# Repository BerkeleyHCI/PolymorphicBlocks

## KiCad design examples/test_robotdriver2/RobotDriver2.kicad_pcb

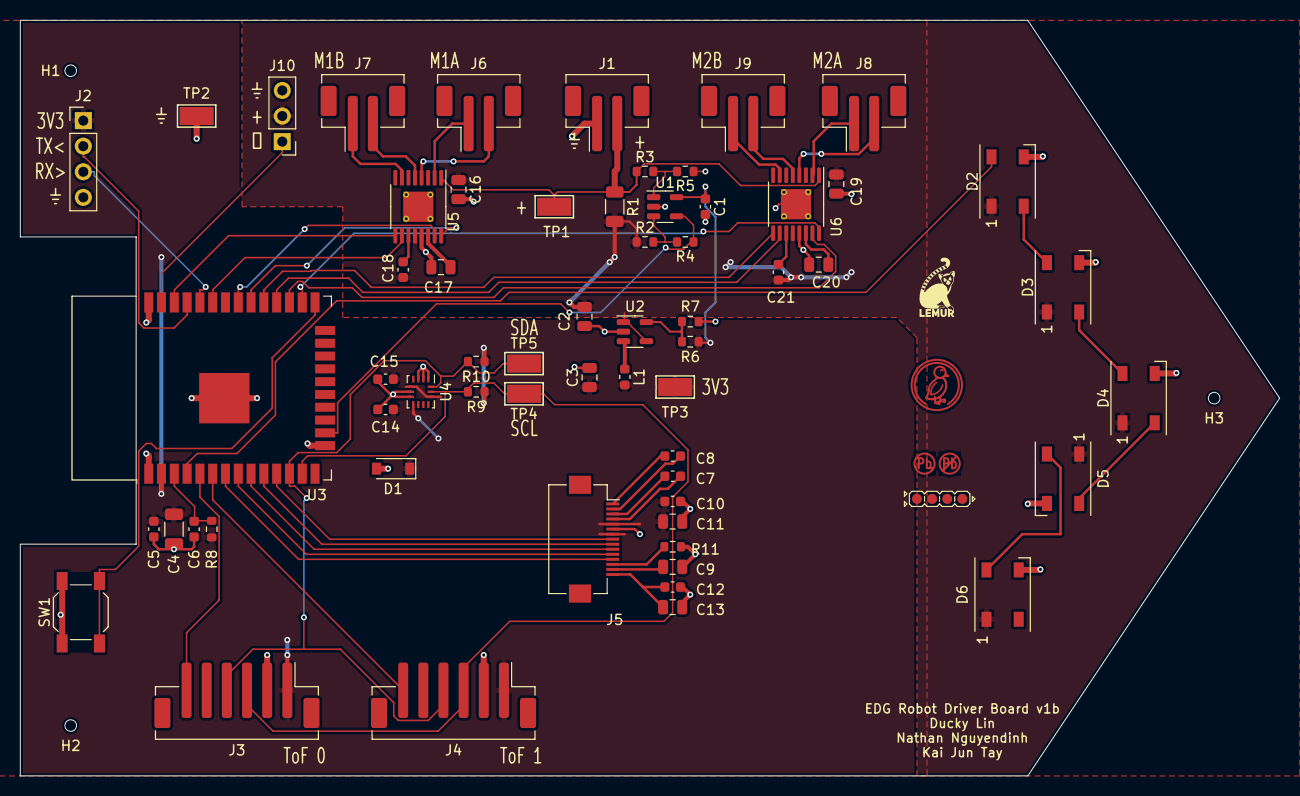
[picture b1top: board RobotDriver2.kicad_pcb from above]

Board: 2 copper layers, 125.0 x 75.0 mm, 68 parts (0 on the bottom side), 55 nets.

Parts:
C1, C5, C7, C8, C10, C12, C14, C15: C14663; C_0603_1608Metric
C2, C3, C9, C11, C17, C20: C1779; C_0805_2012Metric
C4: C5672; C_1206_3216Metric
C6: C15849; C_0603_1608Metric
C13, C16, C19: C15850; C_0805_2012Metric
C18, C21: C57112; C_0603_1608Metric
D1: C499796; D_SOD-123
D2, D3, D4, D5, D6: C2920042; LED_WS2812B_PLCC4_5.0x5.0mm_P3.2mm
H1, H2, H3: JlcToolingHole_1.152mm
J1, J6, J7, J8, J9: C64658; JST_PH_B2B-PH-SM4-TB_1x02-1MP_P2.00mm_Vertical
J2: PinHeader_1x04_P2.54mm_Vertical
J3, J4: C265088; JST_PH_B6B-PH-SM4-TB_1x06-1MP_P2.00mm_Vertical
J5: Hirose_FH12-15S-0.5SH_1x15-1MP_P0.50mm_Horizontal
J10: PinHeader_1x03_P2.54mm_Vertical
L1: C295681; L_0603_1608Metric
R1: C411236; R_1206_3216Metric
R2, R3, R8: C25804; R_0603_1608Metric
R4, R5: C25803; R_0603_1608Metric
R6: C23231; R_0603_1608Metric
R7: C22809; R_0603_1608Metric
R9, R10: C23162; R_0603_1608Metric
R11: C23203; R_0603_1608Metric
SW1: C318884; SW_SPST_SKQG_WithoutStem
TP1, TP2, TP3, TP4, TP5: C238130; TestPoint_Keystone_5015_Micro-Minature
U1: C7972; SOT-23-5
U2: C500769; SOT-23-5
U3: C701342; ESP32-WROOM-32
U4: C967633; Bosch_LGA-14_3x2.5mm_P0.5mm
U5, U6: C50506; TSSOP-16-1EP_4.4x5mm_P0.65mm_EP3x3mm_ThermalVias
U7: Symbol_LemurSmall
U8: Symbol_Duckling
U9: Indicator_LeadFree
U10: Indicator_IdDots_4

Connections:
batt.pins.2: J1.2, R1.1, R3.1, TP1.1, U5.1, U6.1
gnd: C1.2, C2.2, C3.2, C4.2, C5.2, C6.2, C9.2, C10.2, C11.2, C12.2, C13.2, C14.2, C15.2, C16.2, C17.2, C19.2, C20.2, D1.2, D2.3, D3.3, D4.3, D5.3, D6.3, J1.1, J2.4, J3.2, J4.2, J5.6, J10.3, R5.1, R7.2, R11.2, SW1.1, TP2.1, U1.2, U2.2, U3.1, U3.15, U3.38, U3.39, U4.1, U4.2, U4.3, U4.6, U4.7, U5.13, U5.17, U6.13, U6.17
i2c_chain_0.scl: J3.3, J4.3, R9.2, TP4.1, U3.13, U4.13
i2c_chain_0.sda: J3.4, J4.4, R10.2, TP5.1, U3.12, U4.14
isense.amp.(adapter)rf.b.dst: R2.2, R4.2, U1.3
isense.amp.rg.b: R3.2, R5.2, U1.1
lcd.c2_cap.neg: C8.2, J5.2
lcd.device.c1n: C7.2, J5.4
lcd.device.c1p: C7.1, J5.3
lcd.device.c2p: C8.1, J5.1
lcd.device.iref: J5.13, R11.1
lcd.device.vcomh: C9.1, J5.14
lcd.spi.mosi: J5.12, U3.7
lcd.spi.sck: J5.11, U3.8
lcd.vcc_cap2.pos: C12.1, C13.1, J5.15
m1_a.pins.1: J6.1, U5.2
m1_a.pins.2: J6.2, U5.4
m1_b.pins.1: J7.1, U5.7
m1_b.pins.2: J7.2, U5.5
m2_a.pins.1: J8.1, U6.2
m2_a.pins.2: J8.2, U6.4
m2_b.pins.1: J9.1, U6.7
m2_b.pins.2: J9.2, U6.5
mcu.adc.isense: R4.1, U1.4, U3.16
mcu.en_pull.output: C6.1, R8.2, U3.3
mcu.gpio.lcd_cs: J5.8, U3.11
mcu.gpio.lcd_dc: J5.10, U3.9
mcu.gpio.lcd_reset: J5.9, U3.10
mcu.gpio.ledArray: D2.4, U3.4
mcu.gpio.motor_1a1: U3.30, U5.16
mcu.gpio.motor_1a2: U3.31, U5.15
mcu.gpio.motor_1b1: U3.36, U5.9
mcu.gpio.motor_1b2: U3.33, U5.10
mcu.gpio.motor_2a1: U3.26, U6.16
mcu.gpio.motor_2a2: U3.27, U6.15
mcu.gpio.motor_2b1: U3.29, U6.9
mcu.gpio.motor_2b2: U3.28, U6.10
mcu.gpio.pwm: J10.1, U3.37
mcu.gpio.tof_xshut_0: J3.6, U3.5
mcu.gpio.tof_xshut_1: J4.6, U3.6
mcu.prog.out: SW1.2, U3.25
mcu.uart0.uart.rx: J2.2, U3.35
mcu.uart0.uart.tx: J2.3, U3.34
motor_driver1.ic.vcp: C18.1, U5.11
motor_driver1.vint_cap.pwr: C17.1, U5.14
motor_driver2.ic.vcp: C21.1, U6.11
motor_driver2.vint_cap.pwr: C20.1, U6.14
reg_3v3.fb.center: R6.2, R7.1, U2.5
reg_3v3.power_path.switch: L1.1, U2.3
v3v3: C1.1, C3.1, C4.1, C5.1, C10.1, C11.1, C14.1, C15.1, D1.1, J2.1, J3.1, J4.1, J5.5, J5.7, L1.2, R6.1, R8.1, R9.1, R10.1, TP3.1, U1.5, U3.2, U4.5, U4.8, U4.12
vbatt: C2.1, C16.1, C18.2, C19.1, C21.2, D2.1, D3.1, D4.1, D5.1, D6.1, J10.2, R1.2, R2.1, U2.1, U2.4, U5.12, U6.12
ws2812bArray.led[1].din: D2.2, D3.4
ws2812bArray.led[1].dout: D3.2, D4.4
ws2812bArray.led[3].din: D4.2, D5.4
ws2812bArray.led[4].din: D5.2, D6.4

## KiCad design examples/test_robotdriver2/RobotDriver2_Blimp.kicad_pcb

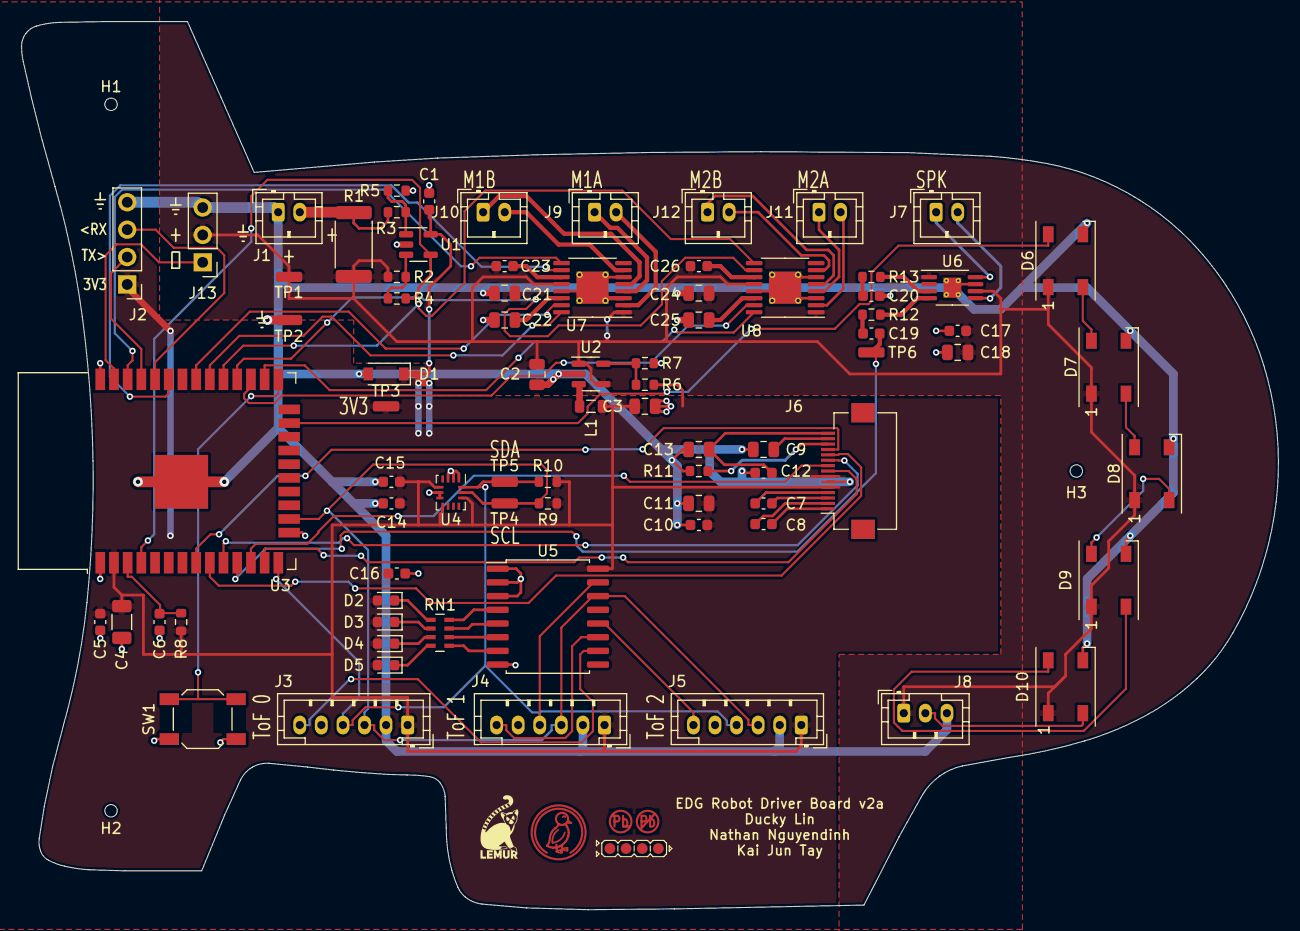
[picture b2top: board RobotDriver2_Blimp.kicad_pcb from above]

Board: 2 copper layers, 116.5 x 82.3 mm, 86 parts (0 on the bottom side), 72 nets.

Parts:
C1, C5, C7, C8, C10, C12, C14, C15, C16, C17: C14663; C_0603_1608Metric
C2, C3, C9, C11, C18, C22, C25: C1779; C_0805_2012Metric
C4: C5672; C_1206_3216Metric
C6, C19, C20: C15849; C_0603_1608Metric
C13, C21, C24: C15850; C_0805_2012Metric
C23, C26: C57112; C_0603_1608Metric
D1: C499796; D_SOD-123
D2, D3, D4, D5: C2286; LED_0603_1608Metric
D6, D7, D8, D9, D10: C2920042; LED_WS2812B_PLCC4_5.0x5.0mm_P3.2mm
H1, H2, H3: JlcToolingHole_1.152mm
J1, J7, J9, J10, J11, J12: JST_PH_B2B-PH-K_1x02_P2.00mm_Vertical
J2: PinHeader_1x04_P2.54mm_Vertical
J3, J4, J5: JST_PH_B6B-PH-K_1x06_P2.00mm_Vertical
J6: Hirose_FH12-15S-0.5SH_1x15-1MP_P0.50mm_Horizontal
J8: JST_PH_B3B-PH-K_1x03_P2.00mm_Vertical
J13: PinHeader_1x03_P2.54mm_Vertical
L1: C98331; L_0805_2012Metric
R1: C305115; R_2512_6332Metric
R2, R3, R8: C25804; R_0603_1608Metric
R4, R5: C25811; R_0603_1608Metric
R6: C23231; R_0603_1608Metric
R7: C22809; R_0603_1608Metric
R9, R10: C23162; R_0603_1608Metric
R11: C23203; R_0603_1608Metric
R12, R13: C22984; R_0603_1608Metric
RN1: C20197; R_Array_Concave_4x0603
SW1: C318884; SW_SPST_SKQG_WithoutStem
TP1, TP2, TP3, TP4, TP5, TP6: TestPoint_TE_RCU_0603
U1: C7972; SOT-23-5
U2: C500769; SOT-23-5
U3: C701342; ESP32-WROOM-32
U4: C967633; Bosch_LGA-14_3x2.5mm_P0.5mm
U5: C86832; SOIC-16W_7.5x10.3mm_P1.27mm
U6: C27396; MSOP-8-1EP_3x3mm_P0.65mm_EP1.68x1.88mm_ThermalVias
U7, U8: C50506; TSSOP-16-1EP_4.4x5mm_P0.65mm_EP3x3mm_ThermalVias
U9: Symbol_LemurSmall
U10: Symbol_Duckling
U11: Indicator_LeadFree
U12: Indicator_IdDots_4

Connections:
batt.pins.2: J1.2, R1.1, R3.1
expander.io.led_1: RN1.7, U5.5
expander.io.led_2: RN1.6, U5.6
expander.io.tof_xshut_0: J3.6, U5.10
expander.io.tof_xshut_1: J4.6, U5.11
gnd: C1.2, C2.2, C3.2, C4.2, C5.2, C6.2, C9.2, C10.2, C11.2, C12.2, C13.2, C14.2, C15.2, C16.2, C17.2, C18.2, C20.2, C21.2, C22.2, C24.2, C25.2, D1.2, D6.3, D7.3, D8.3, D9.3, D10.3, J1.1, J2.4, J3.2, J4.2, J5.2, J6.6, J8.3, J13.3, R5.1, R7.2, R11.2, SW1.1, TP2.1, U1.2, U2.2, U3.1, U3.15, U3.38, U3.39, U4.1, U4.2, U4.3, U4.6, U4.7, U5.1, U5.2, U5.3, U5.8, U6.7, U6.9, U7.3, U7.6, U7.13, U7.17, U8.3, U8.6, U8.13, U8.17
i2c_chain_0.scl: J3.3, J4.3, J5.3, R9.2, TP4.1, U3.16, U4.13, U5.14
i2c_chain_0.sda: J3.4, J4.4, J5.4, R10.2, TP5.1, U3.14, U4.14, U5.15
isense.amp.(adapter)r2.b.src: R3.2, R5.2, U1.1
isense.amp.(adapter)rf.b.src: R2.2, R4.2, U1.3
lcd.c1_cap.pos: C7.1, J6.3
lcd.c2_cap.pos: C8.1, J6.1
lcd.device.c1n: C7.2, J6.4
lcd.device.c2n: C8.2, J6.2
lcd.device.iref: J6.13, R11.1
lcd.spi.mosi: J6.12, U3.8
lcd.spi.sck: J6.11, U3.9
lcd.vcc_cap2.pwr: C12.1, C13.1, J6.15
lcd.vcomh_cap.pos: C9.1, J6.14
led_pixel.pins.2: D10.2, J8.2
led_res.a.0: D2.1, RN1.1
led_res.a.1: D3.1, RN1.2
led_res.a.2: D4.1, RN1.3
led_res.a.3: D5.1, RN1.4
led_res.b.0: RN1.8, U5.4
leds.signals.3: RN1.5, U5.7
m1_a.pins.1: J9.1, U7.4
m1_a.pins.2: J9.2, U7.2
m1_b.pins.1: J10.1, U7.5
m1_b.pins.2: J10.2, U7.7
m2_a.pins.1: J11.1, U8.4
m2_a.pins.2: J11.2, U8.2
m2_b.pins.1: J12.1, U8.5
m2_b.pins.2: J12.2, U8.7
mcu.adc.isense: R4.1, U1.4, U3.4
mcu.gpio.lcd_cs: J6.8, U3.13
mcu.gpio.lcd_dc: J6.10, U3.10
mcu.gpio.lcd_reset: J6.9, U3.12
mcu.gpio.ledArray: D6.4, U3.23
mcu.gpio.motor_1a1: U3.30, U7.16
mcu.gpio.motor_1a2: U3.31, U7.15
mcu.gpio.motor_1b1: U3.36, U7.9
mcu.gpio.motor_1b2: U3.33, U7.10
mcu.gpio.motor_2a1: U3.26, U8.16
mcu.gpio.motor_2a2: U3.27, U8.15
mcu.gpio.motor_2b1: U3.29, U8.9
mcu.gpio.motor_2b2: U3.28, U8.10
mcu.ic.chip_pu: C6.1, R8.2, U3.3
mcu.ic.io0: SW1.2, U3.25
mcu.ic.uart0.tx: J2.2, U3.35
mcu.uart0.uart.tx: J2.3, U3.34
motor_driver1.ic.vcp: C23.1, U7.11
motor_driver1.vint_cap.pwr: C22.1, U7.14
motor_driver2.ic.vcp: C26.1, U8.11
motor_driver2.vint_cap.pwr: C25.1, U8.14
reg_3v3.fb.output: R6.2, R7.1, U2.5
reg_3v3.ic.sw: L1.1, U2.3
servo.pins.1: J13.1, U3.37
spk_chain_0: C19.2, TP6.1, U3.11
spk_chain_1.a: J7.1, U6.8
spk_chain_1.b: J7.2, U6.5
spk_drv.(adapter)inn_res.b.src: R13.2, U6.3
spk_drv.(adapter)inp_res.b.src: R12.2, U6.4
spk_drv.inn_cap.pos: C20.1, R13.1
spk_drv.inp_res.a: C19.1, R12.1
tof.xshut.2: J5.6, U5.12
v3v3: C1.1, C3.1, C4.1, C5.1, C10.1, C11.1, C14.1, C15.1, C16.1, D1.1, D2.2, D3.2, D4.2, D5.2, J2.1, J3.1, J4.1, J5.1, J6.5, J6.7, L1.2, R6.1, R8.1, R9.1, R10.1, TP3.1, U1.5, U3.2, U4.5, U4.8, U4.12, U5.16
vbatt: C2.1, C17.1, C18.1, C21.1, C23.2, C24.1, C26.2, D6.1, D7.1, D8.1, D9.1, D10.1, J8.1, J13.2, R1.2, R2.1, TP1.1, U2.1, U2.4, U6.1, U6.6, U7.1, U7.12, U8.1, U8.12
ws2812bArray.led[1].din: D6.2, D7.4
ws2812bArray.led[1].dout: D7.2, D8.4
ws2812bArray.led[3].din: D8.2, D9.4
ws2812bArray.led[3].dout: D9.2, D10.4

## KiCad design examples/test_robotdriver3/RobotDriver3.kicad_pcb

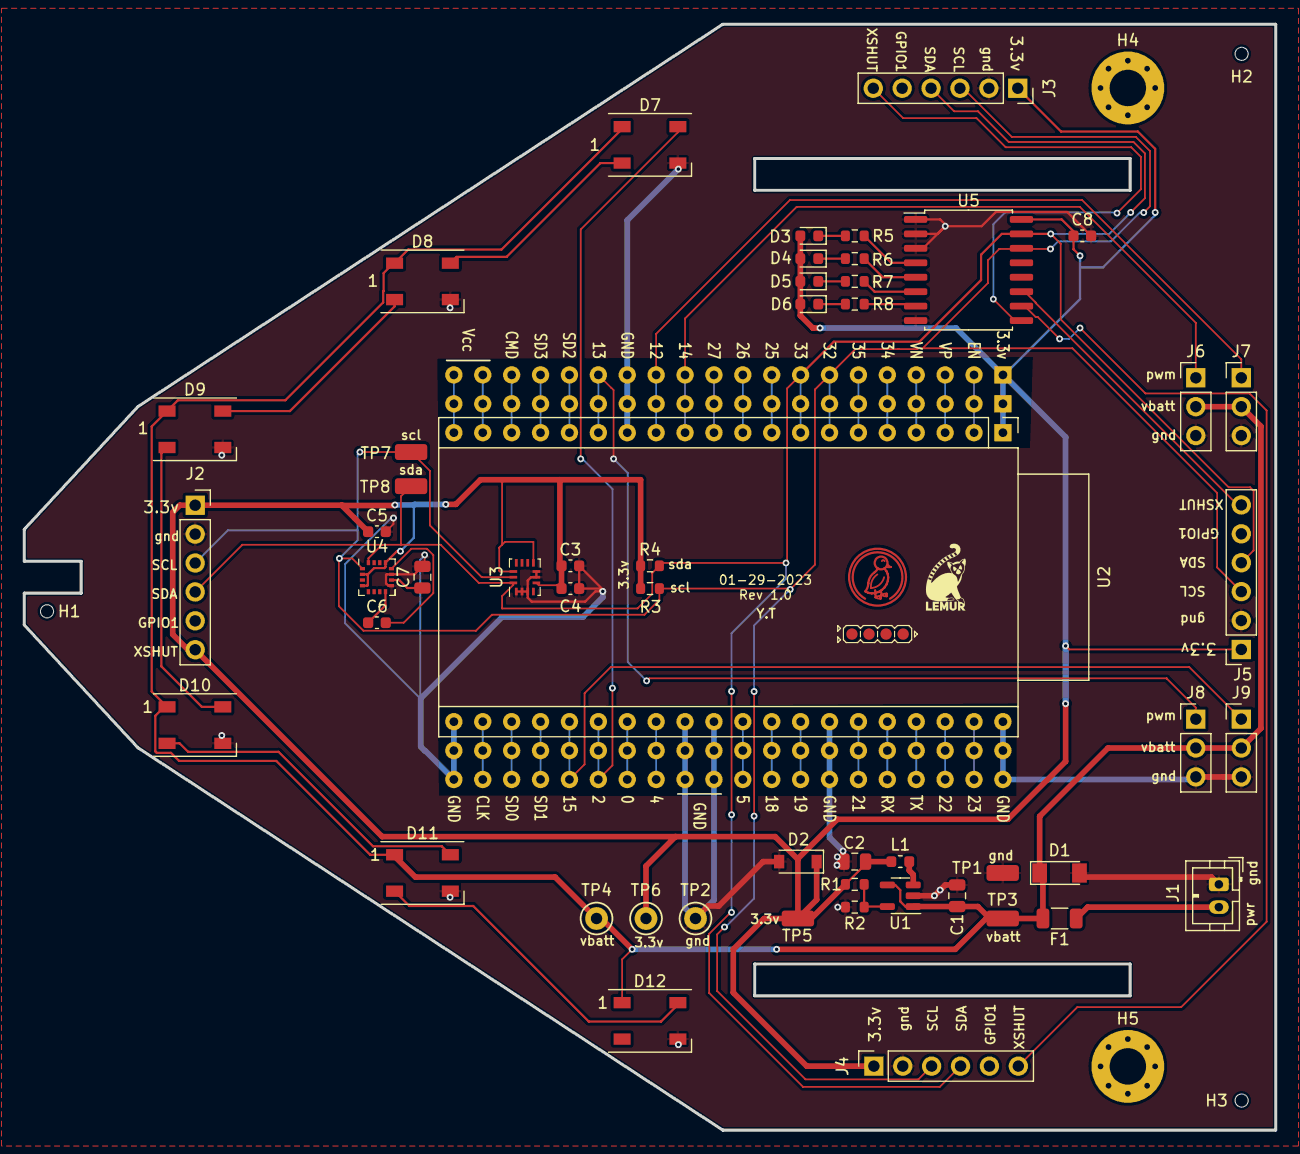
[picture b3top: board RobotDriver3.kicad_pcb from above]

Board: 2 copper layers, 110.0 x 97.2 mm, 60 parts (0 on the bottom side), 32 nets.

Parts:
C1, C2, C7: C_0805_2012Metric
C3, C4, C5, C6, C8: C_0603_1608Metric
D1: ZMM5V6-M (ST(Semtech)) - 100nA@1V 25? Single 5.2V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; D_MiniMELF
D2: BZT52C3V6 (SMC(Sangdest Microelectronicstronic (N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; D_SOD-123
D3, D4, D5, D6: KT-0603R (Hubei KENTO Elec) - Red 615~630nm 1.9~2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; LED_0603_1608Metric
D7, D8, D9, D10, D11, D12: WS2812B (Worldsemi); LED_WS2812B_PLCC4_5.0x5.0mm_P3.2mm
F1: MF-NSMF200-2 (BOURNS) - 6V 2A 100A 4A 1206 Resett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; R_1206_3216Metric
H1, H2, H3: JlcToolingHole_1.152mm
H4, H5: M3; MountingHole_3.2mm_M3_Pad_Via
J1: B2B-PH-K (JST); JST_PH_B2B-PH-K_1x02_P2.00mm_Vertical
J2, J3, J4, J5: PinSocket2.54 1x6 (Generic); PinSocket_1x06_P2.54mm_Vertical
J6, J7, J8, J9: PinHeader2.54 1x3 (Generic); PinHeader_1x03_P2.54mm_Vertical
L1: L_0603_1608Metric
R1, R2, R3, R4, R5, R6, R7, R8: R_0603_1608Metric
TP1: 5015 (Keystone) - gnd; TestPoint_TE_RCT_0805
TP2: 5001 (Keystone) - gnd; TestPoint_Keystone_5000-5004_Miniature
TP3: 5015 (Keystone) - vbatt; TestPoint_TE_RCT_0805
TP4: 5001 (Keystone) - vbatt; TestPoint_Keystone_5000-5004_Miniature
TP5: 5015 (Keystone) - v3v3; TestPoint_TE_RCT_0805
TP6: 5001 (Keystone) - v3v3; TestPoint_Keystone_5000-5004_Miniature
TP7: 5015 (Keystone) - i2c_chain_0.scl; TestPoint_TE_RCT_0805
TP8: 5015 (Keystone) - i2c_tp._io_sda_link; TestPoint_TE_RCT_0805
U1: AP3418 (Diodes Incorporated); SOT-23-5
U2: ESP32-WROVER-DEV; ESP32-WROVER-DEV_Chicken
U3: LSM6DS3TR-C (STMicroelectronics); Bosch_LGA-14_3x2.5mm_P0.5mm
U4: QMC5883L (QST); LGA-16_3x3mm_P0.5mm
U5: PCF8574AT (NXP); SOIC-16W_7.5x10.3mm_P1.27mm
U6: Lemur; Symbol_LemurSmall
U7: Duck; Symbol_Duckling
U8: IdDots4; Indicator_IdDots_4

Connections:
batt.pwr: F1.1, J1.2
expander.io.led_0: R5.2, U5.4
expander.io.led_1: R6.2, U5.5
expander.io.led_2: R7.2, U5.6
expander.io.led_3: R8.2, U5.7
expander.io.tof_xshut_1: J3.6, U5.9
expander.io.tof_xshut_2: J4.6, U5.10
expander.io.tof_xshut_3: J5.6, U5.11
gnd: C1.2, C2.2, C3.2, C4.2, C5.2, C7.2, C8.2, D1.2, D2.2, D7.3, D8.3, D9.3, D10.3, D11.3, D12.3, J1.1, J2.2, J3.2, J4.2, J5.2, J6.3, J7.3, J8.3, J9.3, R2.2, TP1.1, TP2.1, U1.2, U2.14, U2.21, U2.29, U2.30, U2.34, U2.40, U3.1, U3.2, U3.3, U3.6, U3.7, U4.9, U4.11, U5.1, U5.2, U5.3, U5.8
i2c_chain_0.scl: J2.3, J3.3, J4.3, J5.3, R3.2, TP7.1, U2.7, U3.13, U4.1, U5.14
i2c_chain_0.sda: J2.4, J3.4, J4.4, J5.4, R4.2, TP8.1, U2.8, U3.14, U4.16, U5.15
leds.led[0].res.a: D3.1, R5.1
leds.led[1].res.a: D4.1, R6.1
leds.led[2].res.a: D5.1, R7.1
leds.led[3].res.a: D6.1, R8.1
mag.c1.pos: C7.1, U4.10
mag.set_cap.neg: C6.2, U4.12
mag.set_cap.pos: C6.1, U4.8
mcu.io2: D7.4, U2.26
reg_3v3.fb.output: R1.2, R2.1, U1.5
reg_3v3.power_path.switch: L1.1, U1.3
servo[0].pwm: J6.1, U2.12
servo[1].pwm: J7.1, U2.13
servo[2].pwm: J8.1, U2.15
servo[3].pwm: J9.1, U2.25
v3v3: C2.1, C3.1, C4.1, C5.1, C8.1, D2.1, D3.2, D4.2, D5.2, D6.2, J2.1, J2.6, J3.1, J4.1, J5.1, L1.2, R1.1, R3.1, R4.1, TP5.1, TP6.1, U2.1, U3.5, U3.8, U3.12, U4.2, U4.4, U4.13, U5.16
vbatt: C1.1, D1.1, D7.1, D8.1, D9.1, D10.1, D11.1, D12.1, F1.2, J6.2, J7.2, J8.2, J9.2, TP3.1, TP4.1, U1.1, U1.4
ws2812bArray.led[0].dout: D7.2, D8.4
ws2812bArray.led[1].dout: D8.2, D9.4
ws2812bArray.led[2].dout: D9.2, D10.4
ws2812bArray.led[3].dout: D10.2, D11.4
ws2812bArray.led[4].dout: D11.2, D12.4

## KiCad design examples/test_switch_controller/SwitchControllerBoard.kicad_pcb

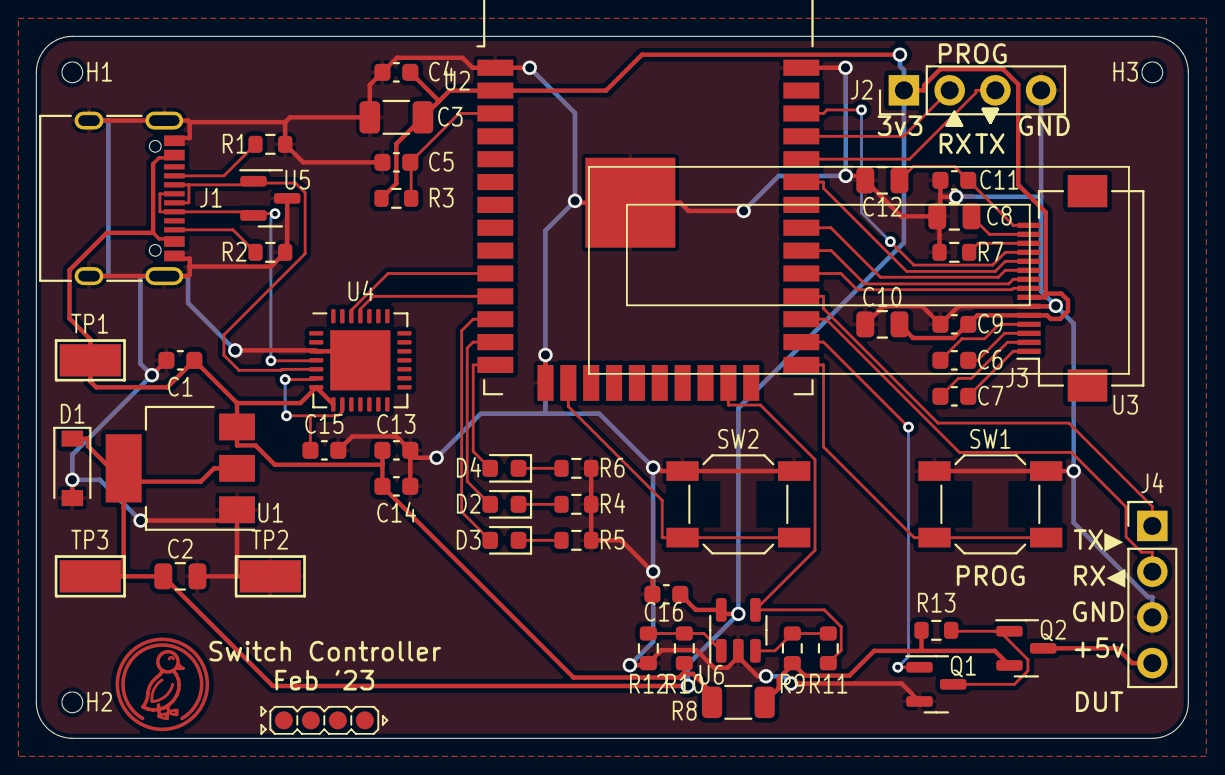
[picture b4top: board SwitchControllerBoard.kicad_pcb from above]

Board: 2 copper layers, 64.0 x 39.0 mm, 55 parts (0 on the bottom side), 42 nets.

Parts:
C1, C4, C5, C6, C7, C9, C11, C13, C14, C15, C16: C_0603_1608Metric
C2, C8, C10, C12: C_0805_2012Metric
C3: C_1206_3216Metric
D1: BZT52C3V6 (SMC(Sangdest Microelectronicstronic (N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; D_SOD-123
D2: KT-0603R (Hubei KENTO Elec) - Red 615~630nm 1.9~2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; LED_0603_1608Metric
D3, D4: LED_0603_1608Metric
H1, H2, H3: JlcToolingHole_1.152mm
J1: COM-15111 (Sparkfun); USB_C_Receptacle_XKB_U262-16XN-4BVC11
J2, J4: PinHeader2.54 1x4 (Generic); PinHeader_1x04_P2.54mm_Vertical
J3: AFC01-S15FCA-00 (Jushuo); Hirose_FH12-15S-0.5SH_1x15-1MP_P0.50mm_Horizontal
Q1: 2N7002 (Changjiang Electronics Tech (CJ)) - 60V 1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; SOT-23
Q2: AO3401A (Alpha & Omega Semicon) - 30V 4A 44m?@10V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; SOT-23
R1, R2, R3, R4, R5, R6, R7, R9, R10, R11, R12, R13: R_0603_1608Metric
R8: R_1206_3216Metric
SW1, SW2: 5.1mm switch; SW_SPST_SKQG_WithoutStem
TP1: 5015 (Keystone) - vusb; TestPoint_Keystone_5015_Micro-Minature
TP2: 5015 (Keystone) - gnd; TestPoint_Keystone_5015_Micro-Minature
TP3: 5015 (Keystone) - v3v3; TestPoint_Keystone_5015_Micro-Minature
U1: LD1117S33TR (STMicroelectronics); SOT-223-3_TabPin2
U2: ESP32-WROOM-32 (Espressif Systems); ESP32-WROOM-32
U3: ER-OLED-0.91-e (EastRising); Lcd_Er_Oled0.91_3_Outline
U4: CP2102 (Silicon Labs); QFN-28-1EP_5x5mm_P0.5mm_EP3.35x3.35mm
U5: PESD5V0X1BT (Nexperia); SOT-23
U6: LMV321 (Texas Instruments); SOT-23-5
U7: Duck; Symbol_Duckling
U8: IdDots4; Indicator_IdDots_4

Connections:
conn.uart.rx: J4.1, U2.28
conn.uart.tx: J4.2, U2.27
gnd: C1.2, C2.2, C3.2, C4.2, C5.2, C8.2, C9.2, C10.2, C11.2, C12.2, C13.2, C14.2, C15.2, C16.2, D1.2, J1.A1, J1.A12, J1.B1, J1.B12, J1.S1, J2.4, J3.6, J4.3, Q1.2, R1.1, R2.1, R4.2, R5.2, R6.2, R7.2, R12.1, SW1.1, SW2.1, TP2.1, U1.1, U2.1, U2.15, U2.38, U2.39, U4.3, U4.29, U5.3, U6.2
isense.amp.r1.b: R9.2, R11.2, U6.3
isense.amp.r2.b: R10.2, R12.2, U6.1
isense.out: R11.1, U2.23, U6.4
isense.pwr_out: Q2.2, R8.2, R9.1, R13.1
lcd.c1_cap.neg: C6.2, J3.4
lcd.c1_cap.pos: C6.1, J3.3
lcd.c2_cap.neg: C7.2, J3.2
lcd.c2_cap.pos: C7.1, J3.1
lcd.cs: J3.8, U2.29
lcd.dc: J3.10, U2.31
lcd.device.vcc: C11.1, C12.1, J3.15
lcd.device.vcomh: C8.1, J3.14
lcd.iref_res.a: J3.13, R7.1
lcd.reset: J3.9, U2.30
lcd.spi.mosi: J3.12, U2.36
lcd.spi.sck: J3.11, U2.33
ledb.res.a: D4.1, R6.1
ledb.signal: D4.2, U2.14
ledg.res.a: D3.1, R5.1
ledg.signal: D3.2, U2.12
ledr.res.a: D2.1, R4.1
ledr.signal: D2.2, U2.13
mcu.ic.chip_pu: C5.1, R3.2, U2.3
mcu.prog.out: SW1.2, U2.25
mcu.uart0.uart.rx: J2.2, U2.35
mcu.uart0.uart.tx: J2.3, U2.34
sw1.out: SW2.2, U2.16
sw.control: Q1.1, U2.26
sw.output: J4.4, Q2.3
sw.pre.drain: Q1.3, Q2.1, R13.2
usb.conn.A5: J1.A5, R1.2
usb.conn.B5: J1.B5, R2.2
usb.usb.dm: J1.A7, J1.B7, U4.5, U5.1
usb.usb.dp: J1.A6, J1.B6, U4.4, U5.2
usb_uart.ic.vdd: C15.1, U4.6, U4.9
usb_uart.uart.rx: U2.11, U4.25
usb_uart.uart.tx: U2.10, U4.26
v3v3: C2.1, C3.1, C4.1, C9.1, C10.1, C16.1, D1.1, J2.1, J3.5, J3.7, R3.1, TP3.1, U1.2, U2.2, U6.5
vusb: C1.1, C13.1, C14.1, J1.A4, J1.A9, J1.B4, J1.B9, R8.1, R10.1, TP1.1, U1.3, U4.7, U4.8

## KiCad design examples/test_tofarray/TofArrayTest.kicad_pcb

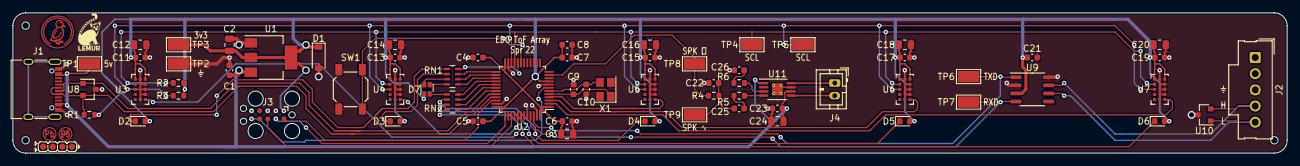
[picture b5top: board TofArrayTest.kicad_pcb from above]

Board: 2 copper layers, 200.0 x 22.0 mm, 74 parts (0 on the bottom side), 47 nets.

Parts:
1: Indicator_LeadFree
2: Indicator_IdDots_4
C1, C4, C5, C6, C11, C13, C15, C17, C19, C21, C23: C14663; C_0603_1608Metric
C2, C3, C12, C14, C16, C18, C20, C24: C1779; C_0805_2012Metric
C7: C57112; C_0603_1608Metric
C8, C25, C26: C15849; C_0603_1608Metric
C9, C10: C1663; C_0603_1608Metric
C22: C1622; C_0603_1608Metric
D1: C499796; D_SOD-123
D2, D3, D4, D5, D6: C2286; LED_0603_1608Metric
D7: C264517; LED_LiteOn_LTST-C19HE1WT
H1, H2, H3: JlcToolingHole_1.152mm
J1: C165948; USB_C_Receptacle_XKB_U262-16XN-4BVC11
J2: Molex_SL_171971-0005_1x05_P2.54mm_Vertical
J3: Tag-Connect_TC2050-IDC-FP_2x05_P1.27mm_Vertical
J4: JST_PH_B2B-PH-K_1x02_P2.00mm_Vertical
R1: C22843; R_0603_1608Metric
R2, R3: C23162; R_0603_1608Metric
R4: C21190; R_0603_1608Metric
R5, R6: C22984; R_0603_1608Metric
RN1, RN2: C20197; R_Array_Concave_4x0603
SW1: C318884; SW_SPST_SKQG_WithoutStem
TP1, TP2, TP3, TP4, TP5, TP6, TP7, TP8, TP9: C238130; TestPoint_Keystone_5015_Micro-Minature
U1: C86781; SOT-223-3_TabPin2
U2: C8734; LQFP-48_7x7mm_P0.5mm
U3, U4, U5, U6, U7: C91199; ST_VL53L0X
U8: C87911; SOT-23
U9: C12084; SO-8_3.9x4.9mm_P1.27mm
U10: SOT-23
U11: C27396; MSOP-8-1EP_3x3mm_P0.65mm_EP1.68x1.88mm_ThermalVias
U12: Symbol_Duckling
U13: Symbol_LemurSmall
X1: C9002; Crystal_SMD_3225-4Pin_3.2x2.5mm

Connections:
can_chain_0.rxd: TP7.1, U2.45, U9.4
can_chain_0.txd: TP6.1, U2.46, U9.1
can_chain_1.canh: J2.4, U9.7, U10.2
can_chain_1.canl: J2.5, U9.6, U10.1
gnd: C1.2, C2.2, C3.2, C4.2, C5.2, C6.2, C7.2, C8.2, C9.2, C10.2, C11.2, C12.2, C13.2, C14.2, C15.2, C16.2, C17.2, C18.2, C19.2, C20.2, C21.2, C22.2, C23.2, C24.2, C26.2, D1.2, J1.A1, J1.A12, J1.B1, J1.B12, J2.3, J3.2, J3.3, J3.5, SW1.1, TP2.1, U1.1, U2.8, U2.23, U2.35, U2.44, U2.47, U3.2, U3.3, U3.4, U3.6, U3.12, U4.2, U4.3, U4.4, U4.6, U4.12, U5.2, U5.3, U5.4, U5.6, U5.12, U6.2, U6.3, U6.4, U6.6, U6.12, U7.2, U7.3, U7.4, U7.6, U7.12, U8.3, U9.2, U9.8, U10.3, U11.7, U11.9, X1.2, X1.4
i2c_chain_0.scl: R2.2, TP4.1, U2.21, U3.10, U4.10, U5.10, U6.10, U7.10
i2c_chain_0.sda: R3.2, TP5.1, U2.22, U3.9, U4.9, U5.9, U6.9, U7.9
leds_chain_0.0: RN1.8, U2.20
leds_chain_0.1: RN1.7, U2.25
leds_chain_0.2: RN2.7, U2.29
leds_chain_0.3: RN2.6, U2.30
leds_chain_0.4: RN2.5, U2.31
leds_chain_0.5: RN1.6, U2.26
leds_chain_0.6: RN1.5, U2.27
leds_chain_0.7: RN2.8, U2.28
mcu.crystal.crystal.a: C9.1, U2.5, X1.1
mcu.gpio.tof_xshut_1: U2.41, U4.5
mcu.gpio.tof_xshut_2: U2.4, U5.5
mcu.gpio.tof_xshut_3: U2.3, U6.5
mcu.ic.osc.xtal_out: C10.1, U2.6, X1.3
mcu.ic.swd.swclk: J3.9, U2.37
mcu.ic.swd.swo: J3.8, U2.39
mcu.swd.swd.reset: J3.6, U2.7
mcu.swd.swd.swdio: J3.10, U2.34
res1.a.0: D2.1, RN1.1
res1.a.1: D3.1, RN1.2
res1.a.2: D7.3, RN1.3
res1.a.3: D7.4, RN1.4
res2.a.0: D7.1, RN2.1
res2.a.1: D4.1, RN2.2
res2.a.2: D5.1, RN2.3
res2.a.3: D6.1, RN2.4
spk_chain_0: R4.1, TP8.1, U2.11
spk_chain_1: C22.1, C25.2, R4.2, TP9.1
spk_chain_2.a: J4.1, U11.8
spk_chain_2.b: J4.2, U11.5
spk_drv.(adapter)inn_res.b.src: R6.2, U11.3
spk_drv.(adapter)inp_res.b.dst: R5.2, U11.4
spk_drv.inn_cap.pos: C26.1, R6.1
spk_drv.inp_res.a: C25.1, R5.1
sw1_chain_0: SW1.2, U2.19
tof.xshut.0: U2.42, U3.5
tof.xshut.4: U2.2, U7.5
usb_chain_0.d_N: J1.A7, J1.B7, U2.32, U8.1
usb_chain_0.d_P: J1.A6, J1.B6, R1.2, U2.33, U8.2
v3v3: C2.1, C3.1, C4.1, C5.1, C6.1, C7.1, C8.1, C11.1, C12.1, C13.1, C14.1, C15.1, C16.1, C17.1, C18.1, C19.1, C20.1, C21.1, D1.1, D2.2, D3.2, D4.2, D5.2, D6.2, D7.2, J3.1, R1.1, R2.1, R3.1, TP3.1, U1.2, U2.1, U2.9, U2.24, U2.36, U2.48, U3.1, U3.11, U4.1, U4.11, U5.1, U5.11, U6.1, U6.11, U7.1, U7.11, U9.3
vusb: C1.1, C23.1, C24.1, J1.A4, J1.A9, J1.B4, J1.B9, TP1.1, U1.3, U11.1, U11.6

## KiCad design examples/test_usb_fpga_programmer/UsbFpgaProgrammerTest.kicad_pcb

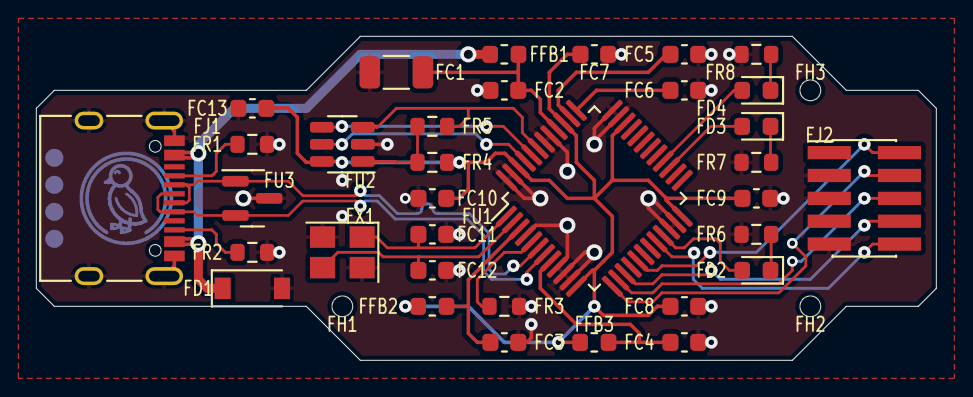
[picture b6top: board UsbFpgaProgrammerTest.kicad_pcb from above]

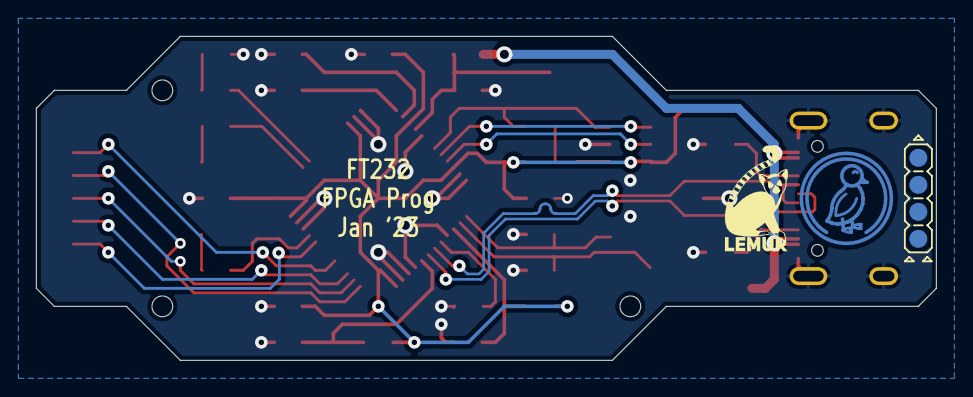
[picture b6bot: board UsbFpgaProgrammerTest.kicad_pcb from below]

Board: 2 copper layers, 50.0 x 18.0 mm, 40 parts (3 on the bottom side), 30 nets.

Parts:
FC1: C_1206_3216Metric
FC2, FC3, FC4, FC5, FC6, FC7, FC8, FC9, FC10, FC11, FC12, FC13: C_0603_1608Metric
FD1: MMSZ5232A_R1_00001 (PANJIT International) - 5?A@3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; D_SOD-123
FD2: C2290 (Hubei KENTO Elec) - White 0603 Light Emitt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; LED_0603_1608Metric
FD3, FD4: LED_0603_1608Metric
FFB1, FFB2, FFB3: L_0603_1608Metric
FH1, FH2, FH3: JlcToolingHole_1.152mm
FJ1: COM-15111 (Sparkfun); USB_C_Receptacle_XKB_U262-16XN-4BVC11
FJ2: PinHeader1.27 Shrouded 2x5 (Generic); PinHeader_2x05_P1.27mm_Vertical_SMD
FR1, FR2, FR3, FR4, FR5, FR6, FR7, FR8: R_0603_1608Metric
FU1: FT232HL (FTDI, Future Technology Devices Internat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; LQFP-48_7x7mm_P0.5mm
FU2: 93LC56B (Microchip Technology); SOT-23-6
FU3: PGB102ST23 (Littelfuse); SOT-23
FU4: Duck; Symbol_Duckling
FU5: Lemur; Symbol_LemurSmall
FU6: IdDots4; Indicator_IdDots_4
FX1: Crystal_SMD_3225-4Pin_3.2x2.5mm

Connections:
ft232.acbus0: FD2.2, FU1.21
ft232.acbus3: FD3.2, FU1.27
ft232.acbus4: FD4.2, FU1.28
ft232.adbus4: FJ2.2, FU1.17
ft232.adbus7: FJ2.10, FU1.20
ft232.crystal.crystal.a: FC11.1, FU1.1, FX1.1
ft232.crystal.crystal.b: FC12.1, FU1.2, FX1.3
ft232.eeprom.cs: FU1.45, FU2.5
ft232.eeprom_spi.eeclk: FU1.44, FU2.4
ft232.eeprom_spi.eedata: FR5.2, FU1.43, FU2.3
ft232.eeprom_spi.spi.miso: FR4.2, FR5.1, FU2.1
ft232.ic.vcca: FC6.1, FU1.37
ft232.ic.vcccore: FC5.1, FU1.38
ft232.ic.vccd: FC7.1, FC8.1, FC9.1, FC10.1, FC13.1, FFB2.1, FFB3.1, FR4.1, FU1.12, FU1.24, FU1.34, FU1.39, FU1.46, FU2.6
ft232.ic.vphy: FC3.1, FFB2.2, FU1.3
ft232.ic.vpll: FC4.1, FFB3.2, FU1.8
ft232.ic.vregin: FC1.1, FC2.1, FFB1.2, FU1.40
ft232.mpsse.miso: FJ2.8, FU1.15
ft232.mpsse.mosi: FJ2.6, FU1.14
ft232.mpsse.sck: FJ2.4, FU1.13
ft232.ref_res.a: FR3.1, FU1.5
gnd: FC1.2, FC2.2, FC3.2, FC4.2, FC5.2, FC6.2, FC7.2, FC8.2, FC9.2, FC10.2, FC11.2, FC12.2, FC13.2, FD1.2, FJ1.A1, FJ1.A12, FJ1.B1, FJ1.B12, FJ1.S1, FJ2.3, FJ2.5, FJ2.9, FR1.1, FR2.1, FR3.2, FR6.2, FR7.2, FR8.2, FU1.4, FU1.9, FU1.10, FU1.11, FU1.22, FU1.23, FU1.35, FU1.36, FU1.41, FU1.42, FU1.47, FU1.48, FU2.2, FU3.3, FX1.2, FX1.4
led0.res.a: FD2.1, FR6.1
led1.res.a: FD3.1, FR7.1
led2.res.a: FD4.1, FR8.1
usb.conn.A5: FJ1.A5, FR1.2
usb.conn.B5: FJ1.B5, FR2.2
usb_chain_0.d_N: FJ1.A7, FJ1.B7, FU1.6, FU3.1
usb_chain_0.d_P: FJ1.A6, FJ1.B6, FU1.7, FU3.2
vusb: FD1.1, FFB1.1, FJ1.A4, FJ1.A9, FJ1.B4, FJ1.B9
